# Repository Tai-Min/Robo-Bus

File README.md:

# Robo-Bus
Modular series of MCUs and hardware boards designed for robotics, providing a unified bus system for seamless and reliable communication between robotic components
test

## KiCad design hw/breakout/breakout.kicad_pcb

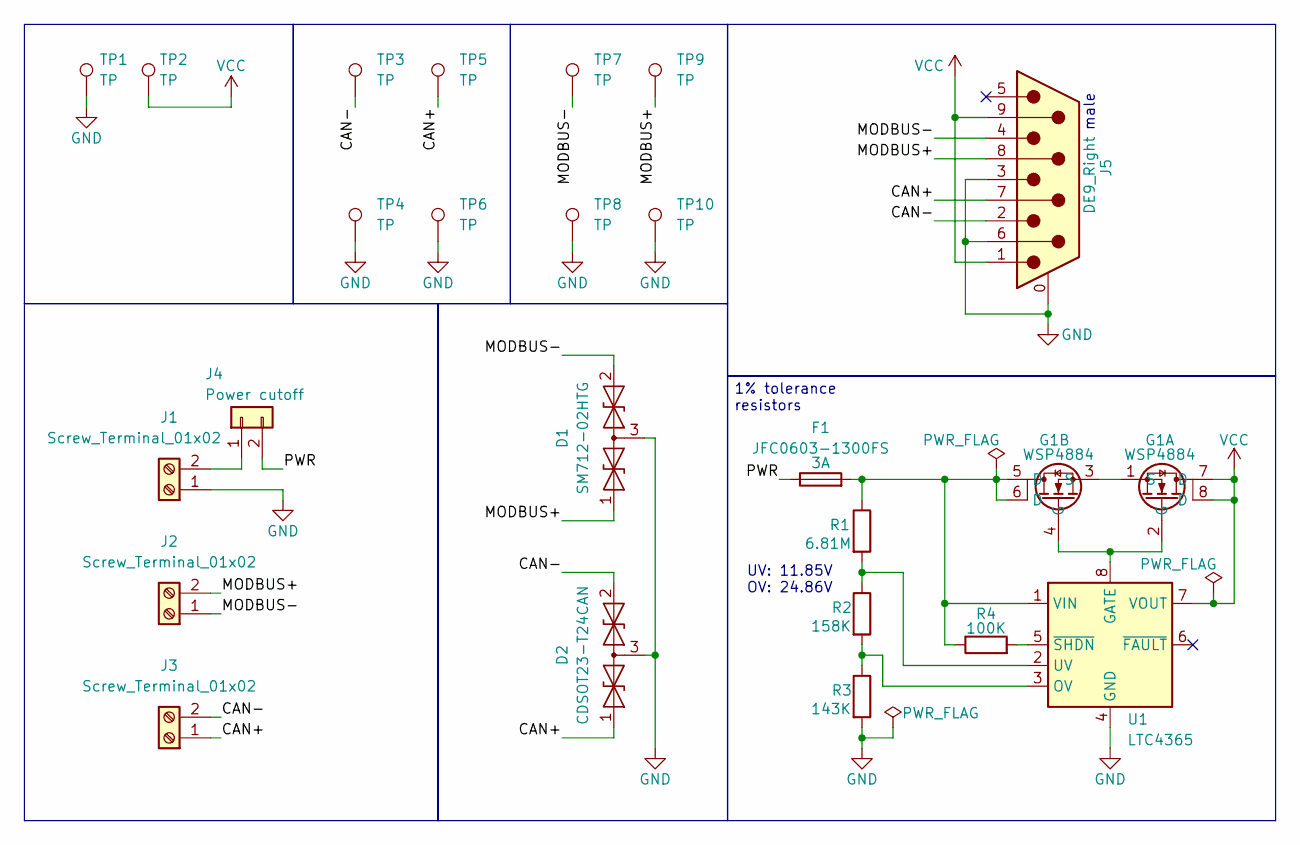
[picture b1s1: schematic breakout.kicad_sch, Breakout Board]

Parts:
D1: SM712-02HTG; SOT-23; LCSC Part # C172881
D2: CDSOT23-T24CAN; SOT-23; LCSC Part # C2959841
F1: JFC0603-1300FS; Fuse_0603_1608Metric_Pad1.05x0.95mm_HandSolder; LCSC Part # C136333
G1: WSP4884; SOIC-8_3.9x4.9mm_P1.27mm; LCSC Part # C148402
J1, J2, J3: Screw_Terminal_01x02; TerminalBlock_Phoenix_MKDS-1,5-2-5.08_1x02_P5.08mm_Horizont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; LCSC Part # C3031437
J4: Power cutoff; PinHeader_1x02_P2.54mm_Vertical; LCSC Part # C7494857
J5: DE9_Right; DSUB-9_Pins_Horizontal_P2.77x2.84mm_EdgePinOffset7.70mm_Hou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; LCSC Part # C19077344
R1: 6.81M; R_0603_1608Metric_Pad0.98x0.95mm_HandSolder; LCSC Part # C54531562
R2: 158K; R_0603_1608Metric_Pad0.98x0.95mm_HandSolder; LCSC Part # C321734
R3: 143K; R_0603_1608Metric_Pad0.98x0.95mm_HandSolder; LCSC Part # C2933146
R4: 100K; R_0603_1608Metric_Pad0.98x0.95mm_HandSolder; LCSC Part # C14675
TP1, TP2, TP3, TP4, TP5, TP6, TP7, TP8, TP9, TP10: TP; TestPoint_THTPad_D2.5mm_Drill1.2mm; LCSC Part # C5277086
U1: LTC4365; TSOT-23-8; LCSC Part # C514441

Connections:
/CAN+: D2.1 (A1), J3.1, J5.7, TP5.1 (1_1)
/CAN-: D2.2 (A2), J3.2, J5.2, TP3.1 (1_1)
/MODBUS+: D1.1 (A1), J2.2, J5.8, TP9.1 (1_1)
/MODBUS-: D1.2 (A2), J2.1, J5.4, TP7.1 (1_1)
/PWR: F1.1, J4.2
GND: D1.3 (common), D2.3 (common), J1.1, J5.0 (PAD), J5.3, J5.6, R3.2, TP1.1 (1_1), TP4.1 (1_1), TP6.1 (1_1), TP8.1 (1_1), TP10.1 (1_1), U1.4 (GND)
unnamed: G1.2 (G), G1.4 (G), U1.8 (GATE)
unnamed: G1.1 (S), G1.3 (S)
unnamed: J1.2, J4.1
unnamed: R2.2, R3.1, U1.3 (OV)
unnamed: R1.2, R2.1, U1.2 (UV)
unnamed: F1.2, G1.5 (D), G1.6 (D), R1.1, R4.1, U1.1 (VIN)
unnamed: R4.2, U1.5 (~SHDN)
VCC: G1.7 (D), G1.8 (D), J5.1, J5.9, TP2.1 (1_1), U1.7 (VOUT)

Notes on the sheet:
UV: 11.85V OV: 24.86V
male
1% tolerance resistors

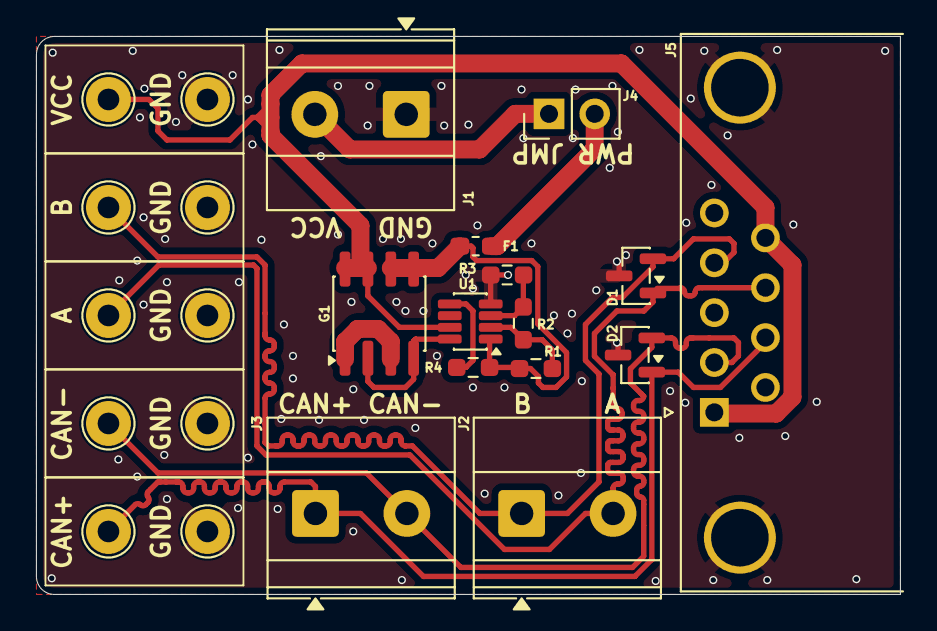
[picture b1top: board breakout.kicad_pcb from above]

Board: 2 copper layers, 48.0 x 31.0 mm, 24 parts (0 on the bottom side), 14 nets.

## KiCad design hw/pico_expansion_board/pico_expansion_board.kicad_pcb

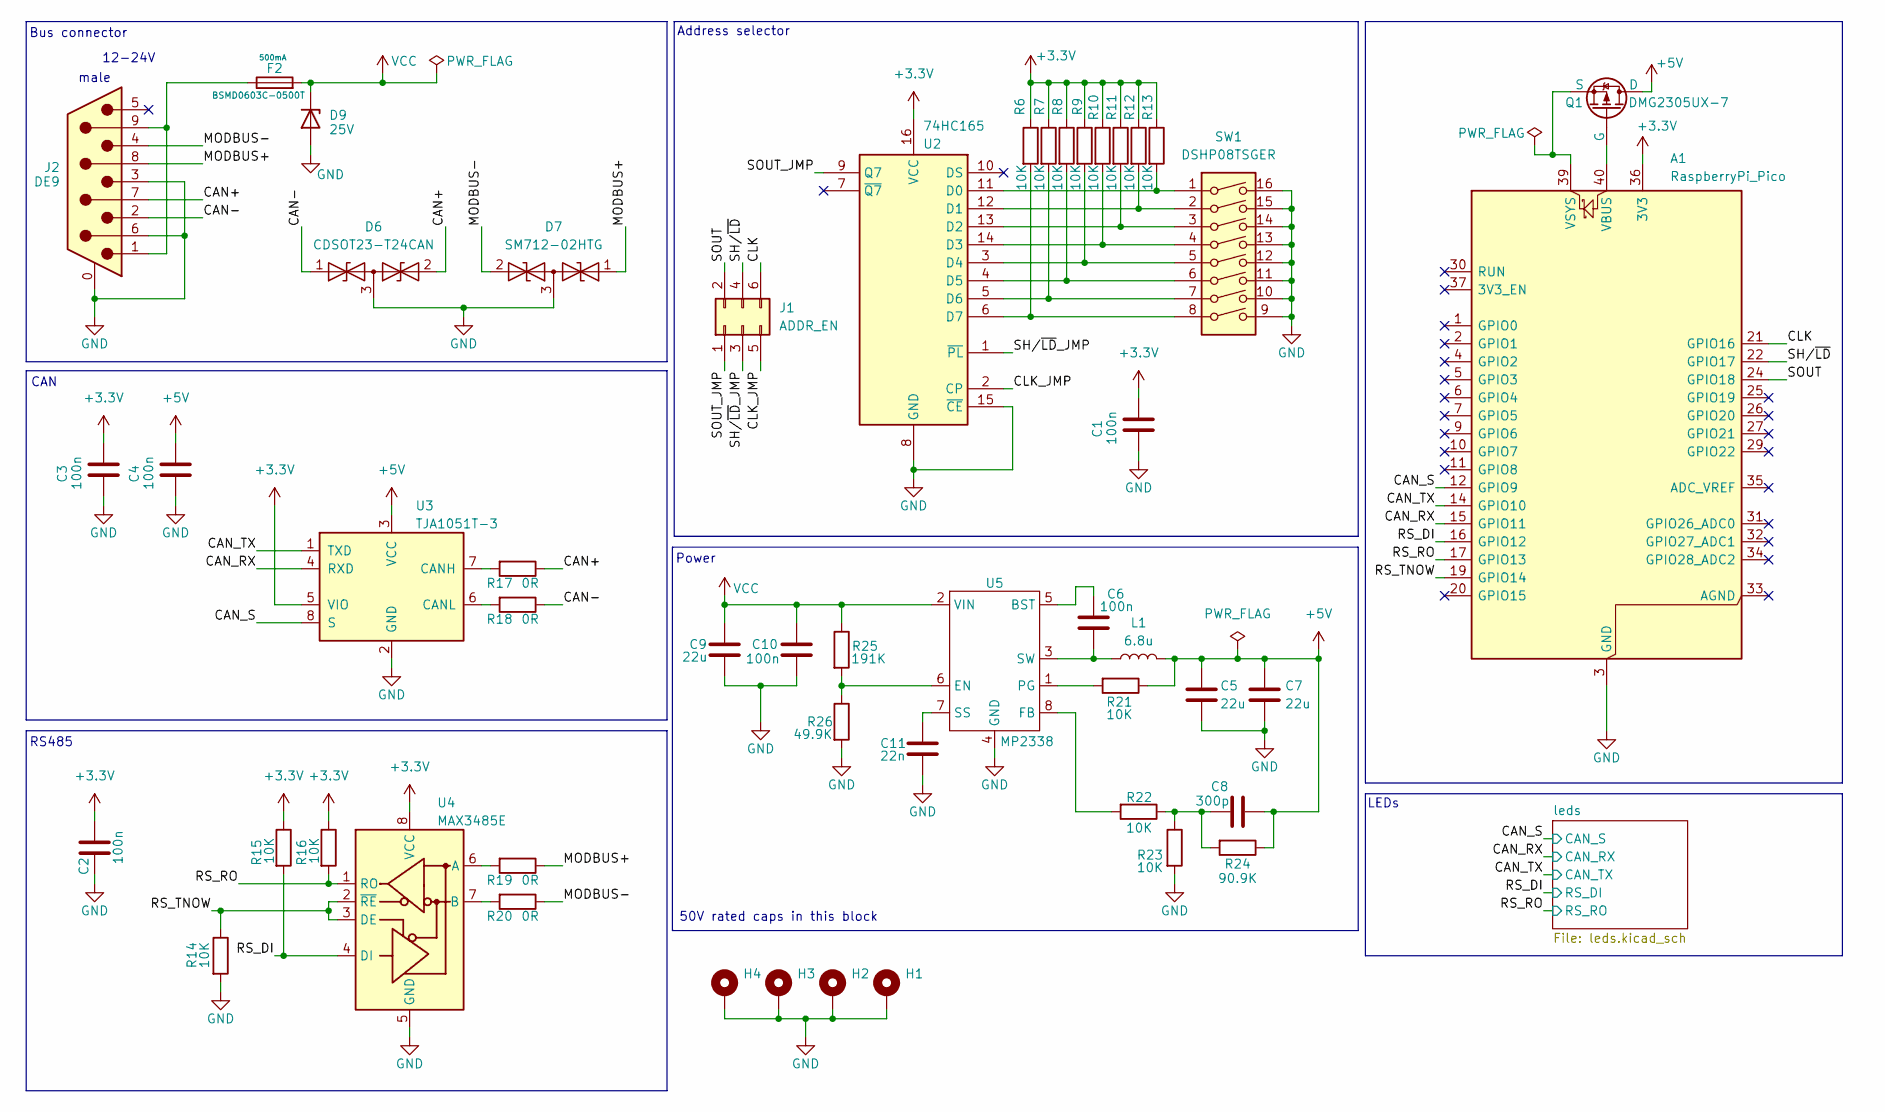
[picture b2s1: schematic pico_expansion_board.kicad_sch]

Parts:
A1: RaspberryPi_Pico; RaspberryPi_Pico_Common_Unspecified
C1, C2, C3, C4, C6, C10: 100n; C_0603_1608Metric; LCSC Part # C14663
C5, C7, C9: 22u; C_1812_4532Metric; LCSC Part # C22388553
C8: 300p; C_0603_1608Metric; LCSC Part # C913766
C11: 22n; C_0603_1608Metric; LCSC Part # C21122
D6: CDSOT23-T24CAN; SOT-23; LCSC Part # C2959841
D7: SM712-02HTG; SOT-23; LCSC Part # C172881
D9: 25V; D_SOD-123; LCSC Part # C525407
F2: BSMD0603C-0500T; Fuse_0603_1608Metric; LCSC Part # C41380225
H1, H2, H3, H4: MountingHole_Pad; MountingHole_3.2mm_M3_Pad_Via
J1: ADDR_EN; PinHeader_2x03_P2.54mm_Vertical; LCSC Part # C7494874
J2: DE9; DSUB-9_Pins_Horizontal_P2.77x2.84mm_EdgePinOffset7.70mm_Hou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; LCSC Part # C19077344
L1: 6.8u; L_APV_ANR4010; LCSC Part # C497571
Q1: DMG2305UX-7; SC-59; LCSC Part # C150470
R6, R7, R8, R9, R10, R11, R12, R13, R14, R15, R16, R21, R22, R23: 10K; R_0603_1608Metric; LCSC Part # C98220
R17, R18, R19, R20: 0R; R_0603_1608Metric; LCSC Part # C95177
R24: 90.9K; R_0603_1608Metric; LCSC Part # C2930136
R25: 191K; R_0603_1608Metric; LCSC Part # C22932
R26: 49.9K; R_0603_1608Metric; LCSC Part # C114624
SW1: DSHP08TSGER; SW_DIP_SPSTx08_Slide_KingTek_DSHP08TS_W7.62mm_P1.27mm; LCSC Part # C3293147
U2: 74HC165; TSSOP-16_4.4x5mm_P0.65mm; LCSC Part # C43420
U3: TJA1051T-3; SOIC-8_3.9x4.9mm_P1.27mm; LCSC Part # C51954344
U4: MAX3485E; SOIC-8_3.9x4.9mm_P1.27mm; LCSC Part # C41369523
U5: MP2338; SOT-583-8

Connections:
+3.3V: A1.36 (3V3), C1.2, C2.2, C3.2, R6.1, R7.1, R8.1, R9.1, R10.1, R11.1, R12.1, R13.1, R15.1, R16.1, U2.16 (VCC), U3.5 (VIO), U4.8 (VCC)
+5V: C4.2, C5.1, C7.1, C8.2, L1.2, Q1.1 (D), R21.1, R24.1, U3.3 (VCC); also elsewhere on the board
/CAN+: D6.2 (A2), J2.7, R17.1
/CAN-: D6.1 (A1), J2.2, R18.1
/CAN_RX: A1.15 (GPIO11), U3.4 (RXD); also elsewhere on the board
/CAN_S: A1.12 (GPIO9), U3.8 (S); also elsewhere on the board
/CAN_TX: A1.14 (GPIO10), U3.1 (TXD); also elsewhere on the board
/CLK: A1.21 (GPIO16), J1.6
/CLK_JMP: J1.5, U2.2 (CP)
/MODBUS+: D7.1 (A1), J2.8, R19.1
/MODBUS-: D7.2 (A2), J2.4, R20.1
/RS_DI: A1.16 (GPIO12), R15.2, U4.4 (DI); also elsewhere on the board
/RS_RO: A1.17 (GPIO13), R16.2, U4.1 (RO); also elsewhere on the board
/RS_TNOW: A1.19 (GPIO14), R14.1, U4.2 (~RE), U4.3 (DE)
/SH/~LD: A1.22 (GPIO17), J1.4
/SH/~LD_JMP: J1.3, U2.1 (~PL)
/SOUT: A1.24 (GPIO18), J1.2
/SOUT_JMP: J1.1, U2.9 (Q7)
GND: A1.3 (GND), A1.8 (GND), A1.13 (GND), A1.18 (GND), A1.23 (GND), A1.28 (GND), A1.38 (GND), C1.1, C2.1, C3.1, C4.1, C5.2, C7.2, C9.2, C10.1, C11.2, D6.3 (common), D7.3 (common), D9.2 (A), H1.1, H2.1, H3.1, H4.1, J2.0 (PAD), J2.3, J2.6, R14.2, R23.2, R26.2, SW1.9, SW1.10, SW1.11, SW1.12, SW1.13, SW1.14, SW1.15, SW1.16, U2.8 (GND), U2.15 (~CE), U3.2 (GND), U4.5 (GND), U5.4 (GND); also elsewhere on the board
unnamed: A1.40 (VBUS), Q1.2 (G)
unnamed: A1.39 (VSYS), Q1.3 (S)
unnamed: C8.1, R22.1, R23.1, R24.2
unnamed: F2.1, J2.1, J2.9
unnamed: R13.2, SW1.1, U2.11 (D0)
unnamed: R12.2, SW1.2, U2.12 (D1)
unnamed: R11.2, SW1.3, U2.13 (D2)
unnamed: R10.2, SW1.4, U2.14 (D3)
unnamed: R9.2, SW1.5, U2.3 (D4)
unnamed: R8.2, SW1.6, U2.4 (D5)
unnamed: R7.2, SW1.7, U2.5 (D6)
unnamed: R6.2, SW1.8, U2.6 (D7)
unnamed: R17.2, U3.7 (CANH)
unnamed: R18.2, U3.6 (CANL)
unnamed: R19.2, U4.6 (A)
unnamed: R20.2, U4.7 (B)
unnamed: C6.2, U5.5 (BST)
unnamed: R25.2, R26.1, U5.6 (EN)
unnamed: R22.2, U5.8 (FB)
unnamed: R21.2, U5.1 (PG)
unnamed: C11.1, U5.7 (SS)
unnamed: C6.1, L1.1, U5.3 (SW)
VCC: C9.1, C10.2, D9.1 (K), F2.2, R25.1, U5.2 (VIN)

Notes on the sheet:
CAN
LEDs
12-24V
50V rated caps in this block
Bus connector
Address selector
male
RS485
Power

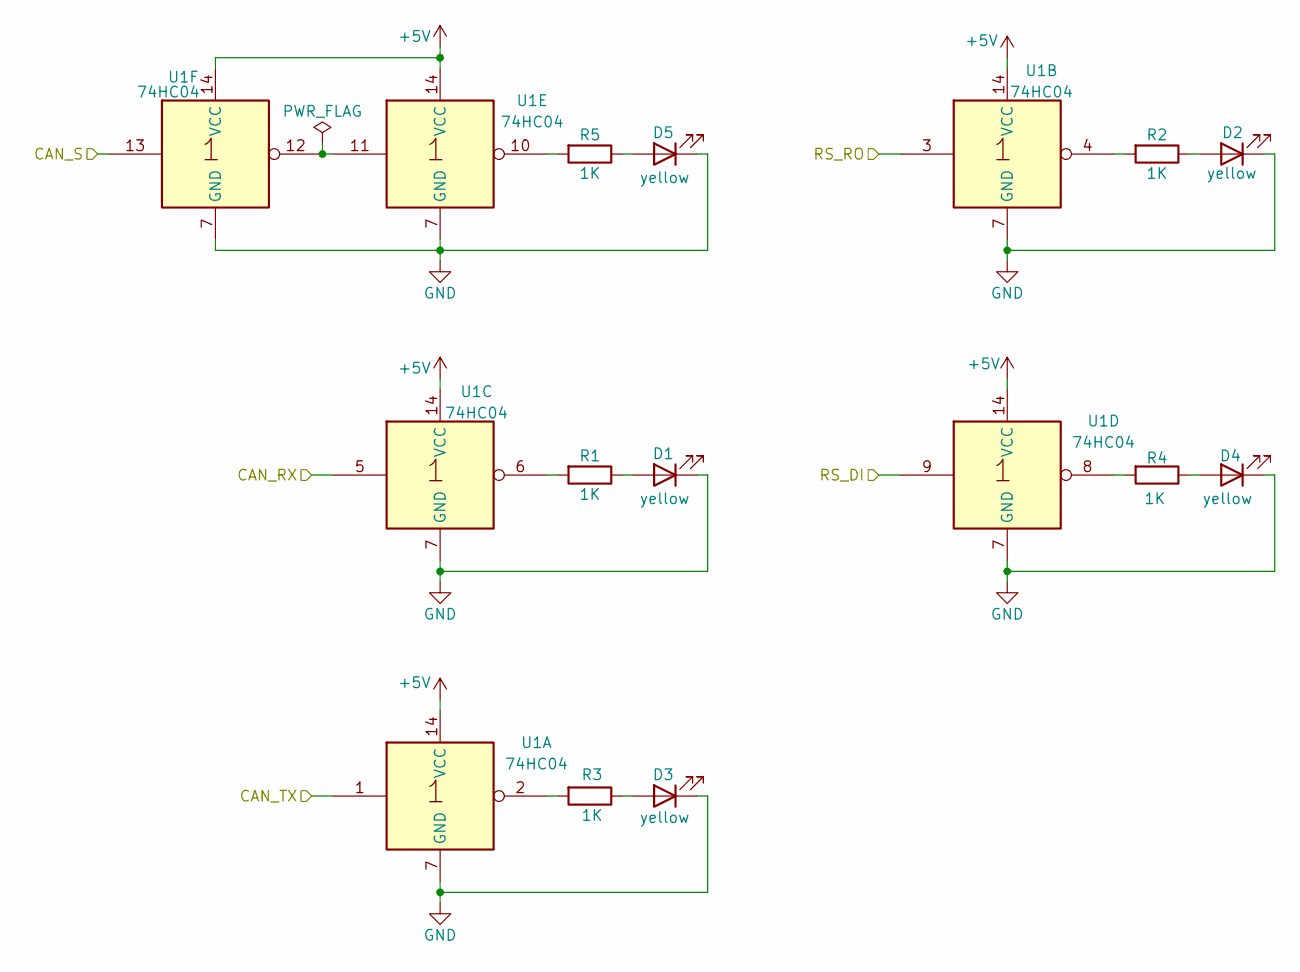
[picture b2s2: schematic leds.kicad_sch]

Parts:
D1, D2, D3, D4, D5: yellow; LED_0603_1608Metric; LCSC Part # C72038
R1, R2, R3, R4, R5: 1K; R_0603_1608Metric; LCSC Part # C22548
U1: 74HC04; TSSOP-14_4.4x5mm_P0.65mm; LCSC Part # C19723773

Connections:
+5V: U1.14 (VCC); also elsewhere on the board
/CAN_RX: U1.5; also elsewhere on the board
/CAN_S: U1.13; also elsewhere on the board
/CAN_TX: U1.1; also elsewhere on the board
/RS_DI: U1.9; also elsewhere on the board
/RS_RO: U1.3; also elsewhere on the board
GND: D1.1 (K), D2.1 (K), D3.1 (K), D4.1 (K), D5.1 (K), U1.7 (GND); also elsewhere on the board
unnamed: D1.2 (A), R1.1
unnamed: D2.2 (A), R2.1
unnamed: D3.2 (A), R3.1
unnamed: D4.2 (A), R4.1
unnamed: D5.2 (A), R5.1
unnamed: R1.2, U1.6
unnamed: R2.2, U1.4
unnamed: R3.2, U1.2
unnamed: R4.2, U1.8
unnamed: R5.2, U1.10
unnamed: U1.11, U1.12

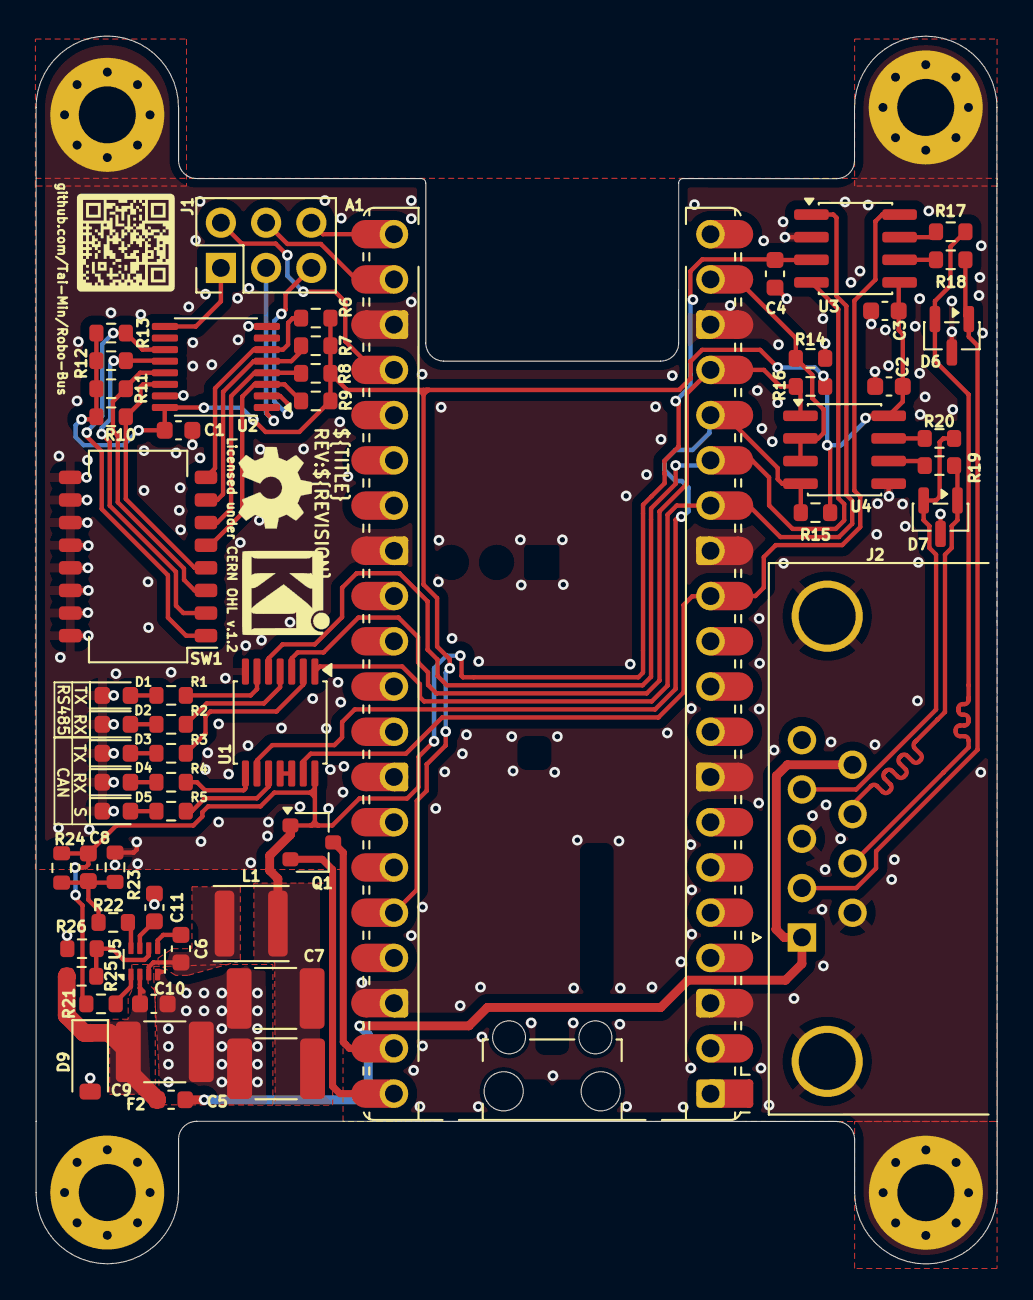
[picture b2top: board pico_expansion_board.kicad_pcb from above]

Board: 2 copper layers, 54.0 x 69.0 mm, 62 parts (0 on the bottom side), 53 nets.

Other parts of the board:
osh: OSHW-Logo2_7.3x6mm_SilkScreen

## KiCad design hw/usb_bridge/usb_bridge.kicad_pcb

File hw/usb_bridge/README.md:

USB <--> CAN part of this pcb is based on [candleLight FD](https://github.com/linux-automation/candleLightFD/tree/main).

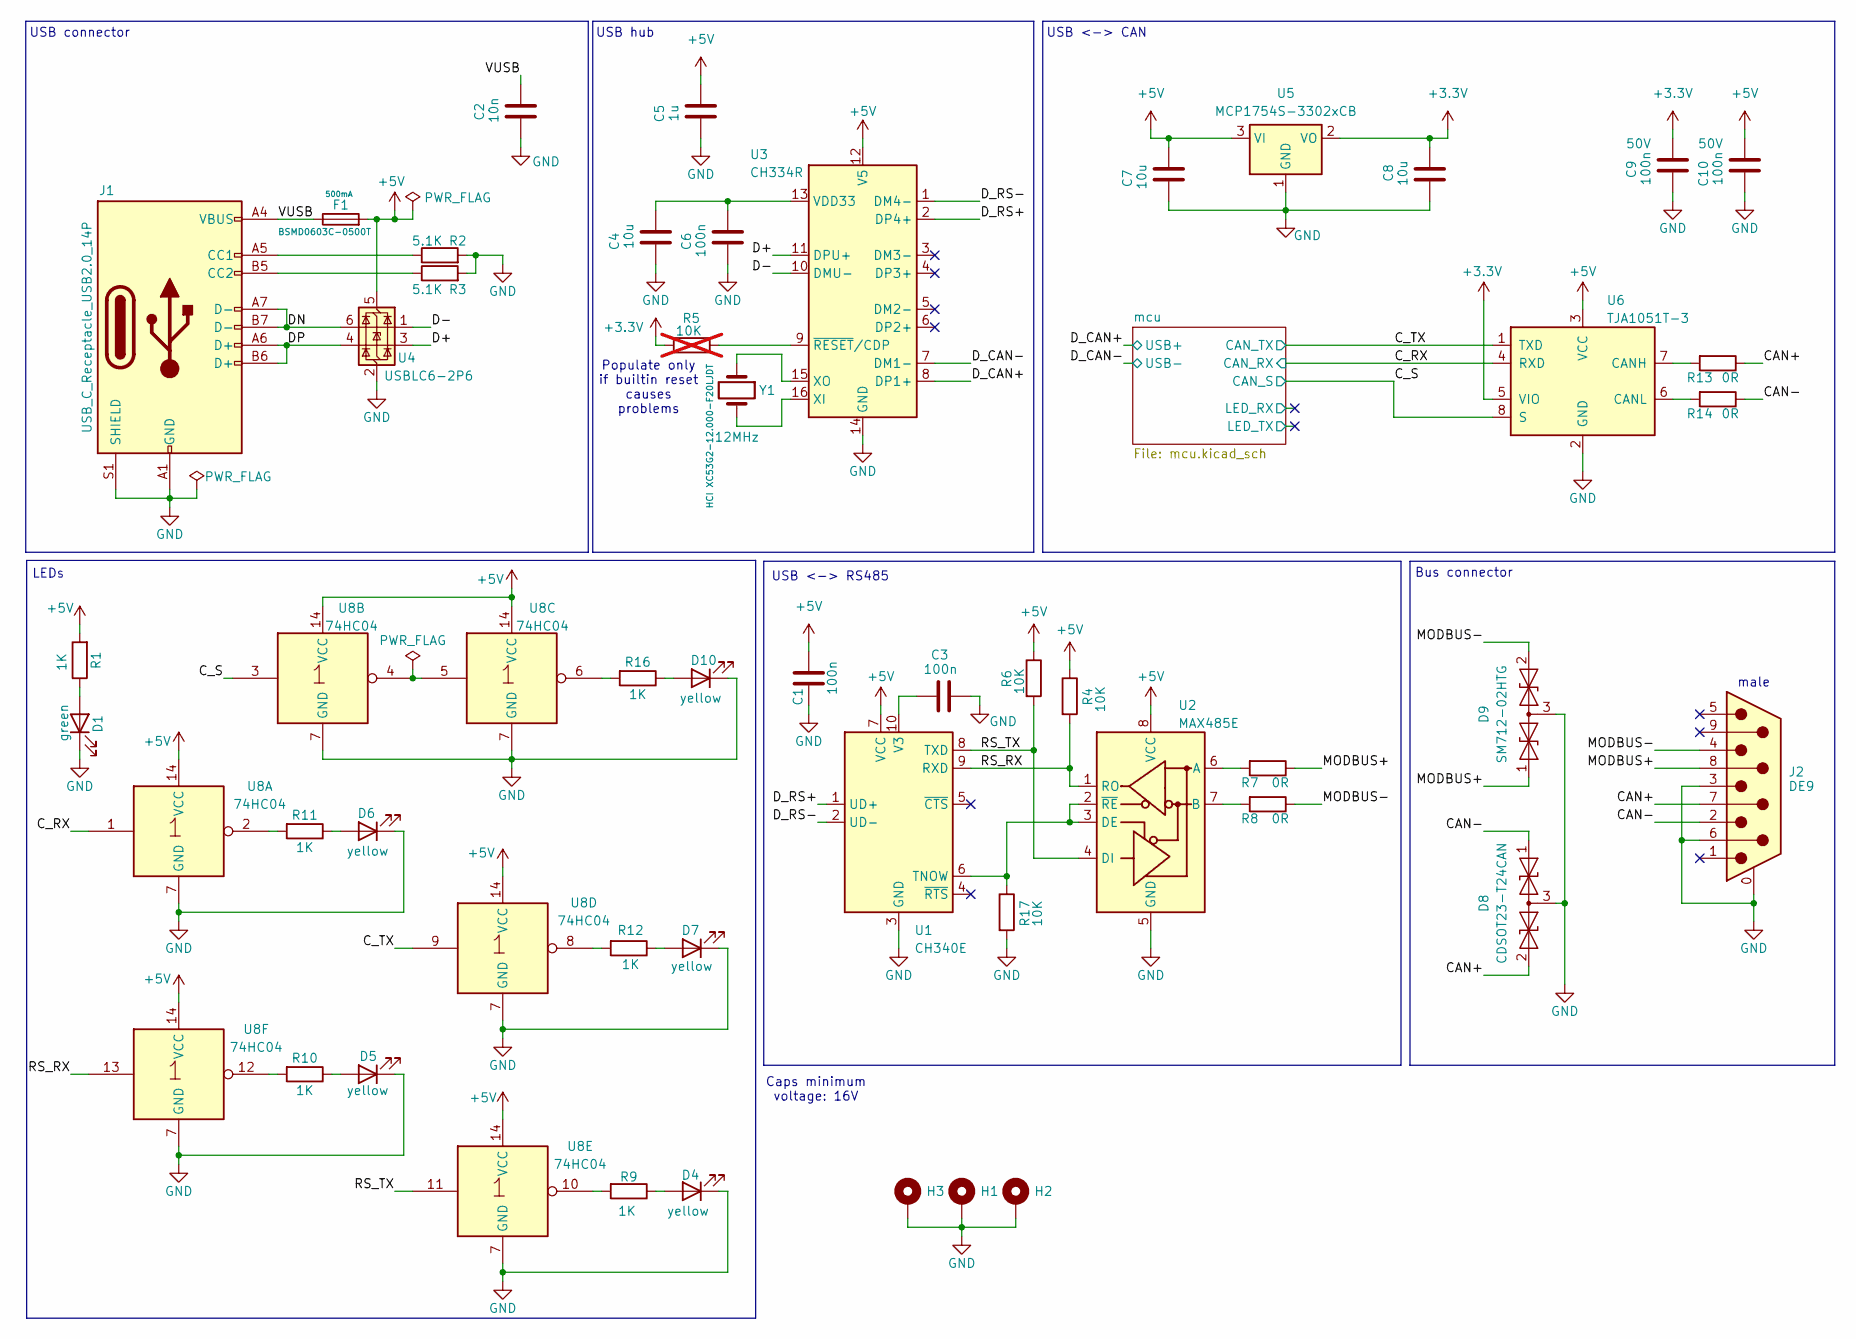
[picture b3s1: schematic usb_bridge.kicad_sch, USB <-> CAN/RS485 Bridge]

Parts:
C1, C3, C6, C9, C10: 100n; C_0603_1608Metric; LCSC Part # C66501
C2: 10n; C_0603_1608Metric; LCSC Part # C100042
C4, C7, C8: 10u; C_0603_1608Metric; LCSC Part # C92487
C5: 1u; C_0603_1608Metric; LCSC Part # C1592
D1: green; LED_0603_1608Metric; LCSC Part # C22371297
D4, D5, D6, D7, D10: yellow; LED_0603_1608Metric; LCSC Part # C72038
D8: CDSOT23-T24CAN; SOT-23; LCSC Part # C2959841
D9: SM712-02HTG; SOT-23; LCSC Part # C172881
F1: BSMD0603C-0500T; Fuse_0603_1608Metric; LCSC Part # C41380225
H1, H2, H3: MountingHole_Pad; MountingHole_3.2mm_M3_Pad_Via
J1: USB_C_Receptacle_USB2.0_14P; USB_C_Receptacle_GCT_USB4085; LCSC Part # C7095263
J2: DE9; DSUB-9_Pins_Horizontal_P2.77x2.84mm_EdgePinOffset7.70mm_Hou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; LCSC Part # C19077344
R1, R9, R10, R11, R12, R16: 1K; R_0603_1608Metric; LCSC Part # C22548
R2, R3: 5.1K; R_0603_1608Metric; LCSC Part # C2907044
R4, R6, R17: 10K; R_0603_1608Metric; LCSC Part # C98220
R5: 10K; R_0603_1608Metric; LCSC Part # C98220; not fitted
R7, R8, R13, R14: 0R; R_0603_1608Metric; LCSC Part # C95177
U1: CH340E; MSOP-10_3x3mm_P0.5mm; LCSC Part # C99652
U2: MAX485E; SOIC-8_3.9x4.9mm_P1.27mm; LCSC Part # C481667
U3: CH334R; QSOP-16_3.9x4.9mm_P0.635mm; LCSC Part # C4154405
U4: USBLC6-2P6; SOT-666; LCSC Part # C15999
U5: MCP1754S-3302xCB; SOT-23; LCSC Part # C625392
U6: TJA1051T-3; SOIC-8_3.9x4.9mm_P1.27mm; LCSC Part # C51954344
U8: 74HC04; TSSOP-14_4.4x5mm_P0.65mm; LCSC Part # C19723773
Y1: HCI XC53G2-12.000-F20LJDT; Crystal_SMD_5032-2Pin_5.0x3.2mm; LCSC Part # C2842275

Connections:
+3.3V: C8.2, C9.2, R5.2, U5.2 (VO), U6.5 (VIO); also elsewhere on the board
+5V: C1.2, C5.2, C7.2, C10.2, F1.2, R1.2, R4.1, R6.1, U1.7 (VCC), U2.8 (VCC), U3.12 (V5), U4.5 (VBUS), U5.3 (VI), U6.3 (VCC), U8.14 (VCC)
/CAN+: D8.2 (A2), J2.7, R13.1
/CAN-: D8.1 (A1), J2.2, R14.1
/C_RX: U6.4 (RXD), U8.1; also elsewhere on the board
/C_S: U6.8 (S), U8.3; also elsewhere on the board
/C_TX: U6.1 (TXD), U8.9; also elsewhere on the board
/D+: U3.11 (DPU+), U4.3 (I/O2)
/D-: U3.10 (DMU-), U4.1 (I/O1)
/DN: J1.A7 (D-), J1.B7 (D-), U4.6 (I/O1)
/DP: J1.A6 (D+), J1.B6 (D+), U4.4 (I/O2)
/D_CAN+: U3.8 (DP1+); also elsewhere on the board
/D_CAN-: U3.7 (DM1-); also elsewhere on the board
/D_RS+: U1.1 (UD+), U3.2 (DP4+)
/D_RS-: U1.2 (UD-), U3.1 (DM4-)
/MODBUS+: D9.1 (A1), J2.8, R7.1
/MODBUS-: D9.2 (A2), J2.4, R8.1
/RS_RX: R4.2, U1.9 (RXD), U2.1 (RO), U8.13
/RS_TX: R6.2, U1.8 (TXD), U2.4 (DI), U8.11
/VUSB: C2.2, F1.1, J1.A4 (VBUS), J1.A9 (VBUS), J1.B4 (VBUS), J1.B9 (VBUS)
GND: C1.1, C2.1, C3.2, C4.1, C5.1, C6.1, C7.1, C8.1, C9.1, C10.1, D1.1 (K), D4.1 (K), D5.1 (K), D6.1 (K), D7.1 (K), D8.3 (common), D9.3 (common), D10.1 (K), H1.1, H2.1, H3.1, J1.A1 (GND), J1.A12 (GND), J1.B1 (GND), J1.B12 (GND), J1.S1 (SHIELD), J2.0 (PAD), J2.3, J2.6, R2.2, R3.2, R17.2, U1.3 (GND), U2.5 (GND), U3.14 (GND), U4.2 (GND), U5.1 (GND), U6.2 (GND), U8.7 (GND); also elsewhere on the board
unnamed: D1.2 (A), R1.1
unnamed: D4.2 (A), R9.1
unnamed: D5.2 (A), R10.1
unnamed: D6.2 (A), R11.1
unnamed: D7.2 (A), R12.1
unnamed: D10.2 (A), R16.1
unnamed: J1.A5 (CC1), R2.1
unnamed: J1.B5 (CC2), R3.1
unnamed: R9.2, U8.10
unnamed: R10.2, U8.12
unnamed: R11.2, U8.2
unnamed: R12.2, U8.8
unnamed: R16.2, U8.6
unnamed: R17.1, U1.6 (TNOW), U2.2 (~RE), U2.3 (DE)
unnamed: C3.1, U1.10 (V3)
unnamed: R7.2, U2.6 (A)
unnamed: R8.2, U2.7 (B)
unnamed: C4.2, C6.2, U3.13 (VDD33)
unnamed: U3.16 (XI), Y1.2
unnamed: U3.15 (XO), Y1.1
unnamed: R5.1, U3.9 (~RESET/CDP)
unnamed: R13.2, U6.7 (CANH)
unnamed: R14.2, U6.6 (CANL)
unnamed: U8.4, U8.5

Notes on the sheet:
Populate only if builtin reset causes problems
USB <-> RS485
Bus connector
male
USB <-> CAN
USB hub
Caps minimum voltage: 16V
LEDs
USB connector

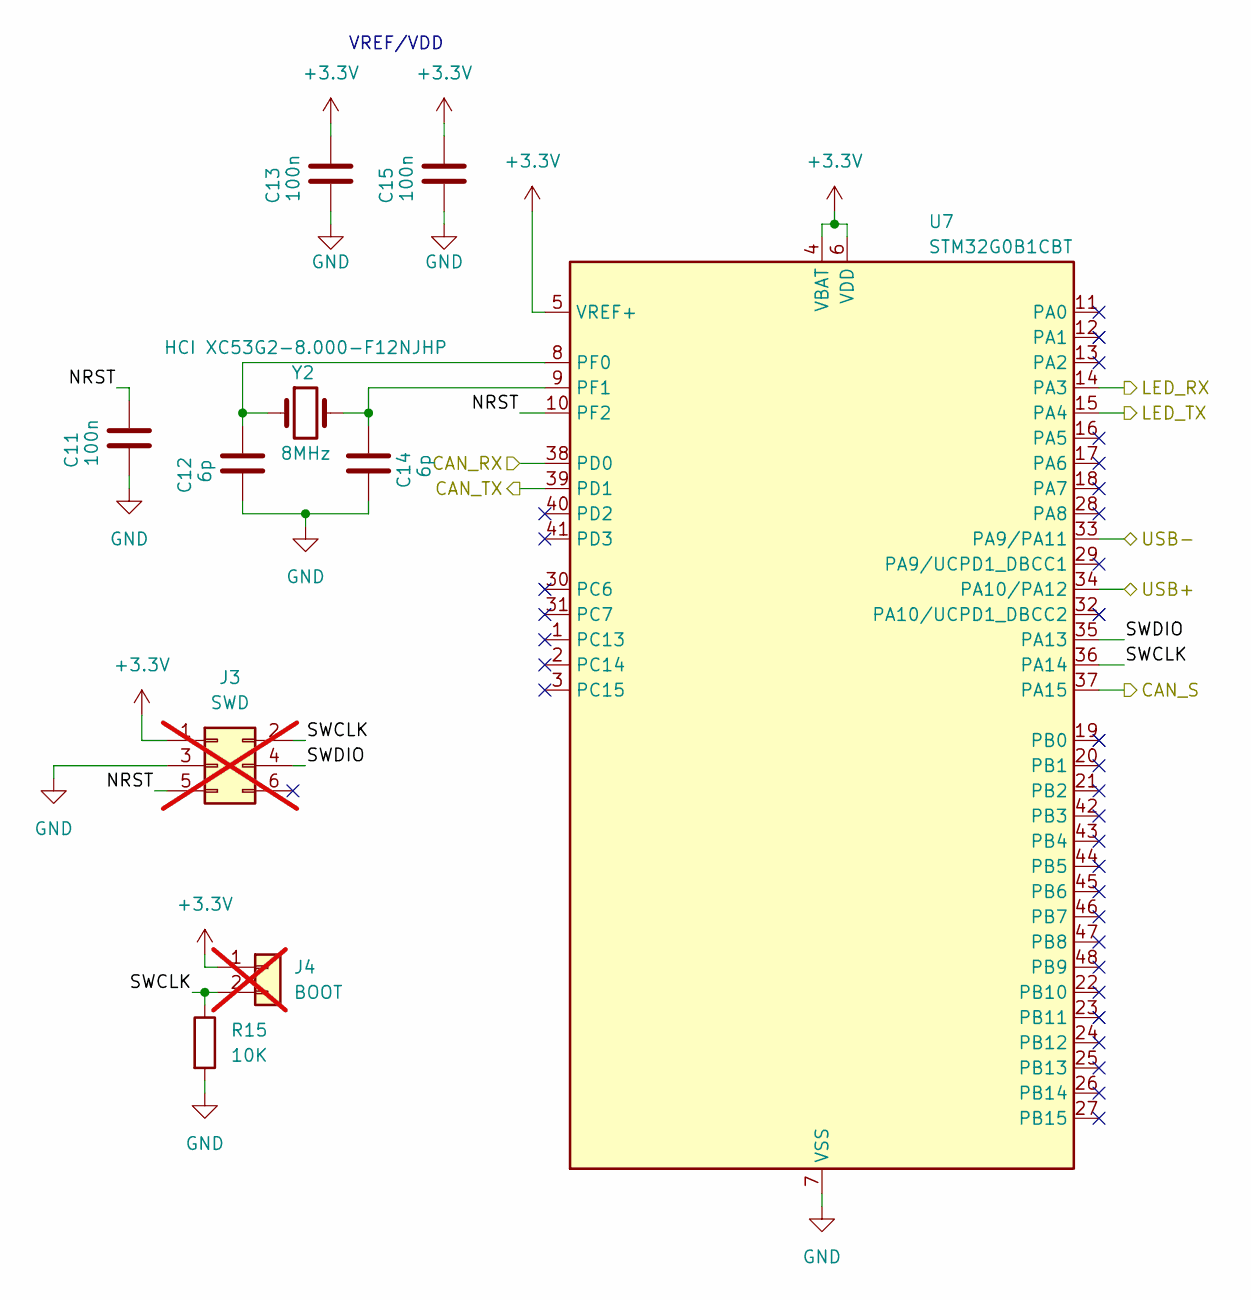
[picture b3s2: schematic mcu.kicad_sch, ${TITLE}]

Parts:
C11, C13, C15: 100n; C_0603_1608Metric; LCSC Part # C66501
C12, C14: 6p; C_0603_1608Metric; LCSC Part # C170142
J3: SWD; PinHeader_2x03_P2.54mm_Vertical; LCSC Part # C7494874; not fitted
J4: BOOT; PinHeader_1x02_P2.54mm_Vertical; LCSC Part # C7494857; not fitted
R15: 10K; R_0603_1608Metric; LCSC Part # C98220
U7: STM32G0B1CBT; LQFP-48_7x7mm_P0.5mm; LCSC Part # C2847904
Y2: HCI XC53G2-8.000-F12NJHP; Crystal_SMD_5032-2Pin_5.0x3.2mm; LCSC Part # C2842269

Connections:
+3.3V: C13.2, C15.2, J3.1, J4.1, U7.4 (VBAT), U7.5 (VREF+), U7.6 (VDD); also elsewhere on the board
/C_RX: U7.38 (PD0); also elsewhere on the board
/C_S: U7.37 (PA15); also elsewhere on the board
/C_TX: U7.39 (PD1); also elsewhere on the board
/D_CAN+: U7.34 (PA10/PA12); also elsewhere on the board
/D_CAN-: U7.33 (PA9/PA11); also elsewhere on the board
/mcu/LED_RX: U7.14 (PA3)
/mcu/LED_TX: U7.15 (PA4)
/mcu/NRST: C11.2, J3.5, U7.10 (PF2)
/mcu/SWCLK: J3.2, J4.2, R15.1, U7.36 (PA14)
/mcu/SWDIO: J3.4, U7.35 (PA13)
GND: C11.1, C12.1, C13.1, C14.1, C15.1, J3.3, R15.2, U7.7 (VSS); also elsewhere on the board
unnamed: C12.2, U7.8 (PF0), Y2.1
unnamed: C14.2, U7.9 (PF1), Y2.2

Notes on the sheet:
VREF/VDD

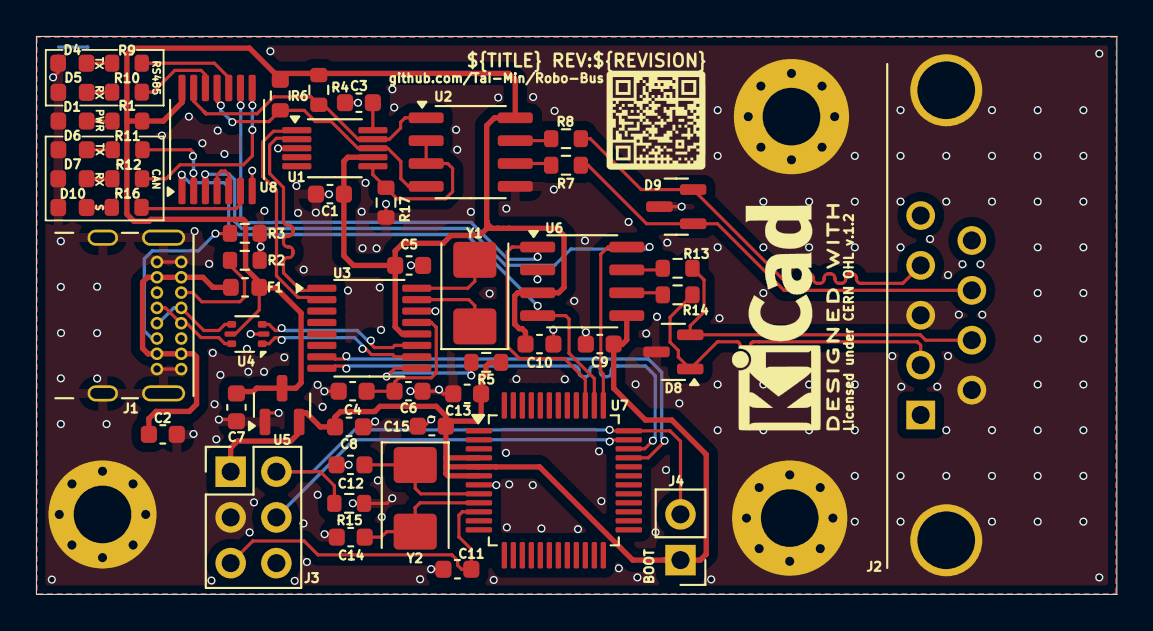
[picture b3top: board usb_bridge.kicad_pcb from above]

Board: 2 copper layers, 60.0 x 31.0 mm, 58 parts (0 on the bottom side), 50 nets.

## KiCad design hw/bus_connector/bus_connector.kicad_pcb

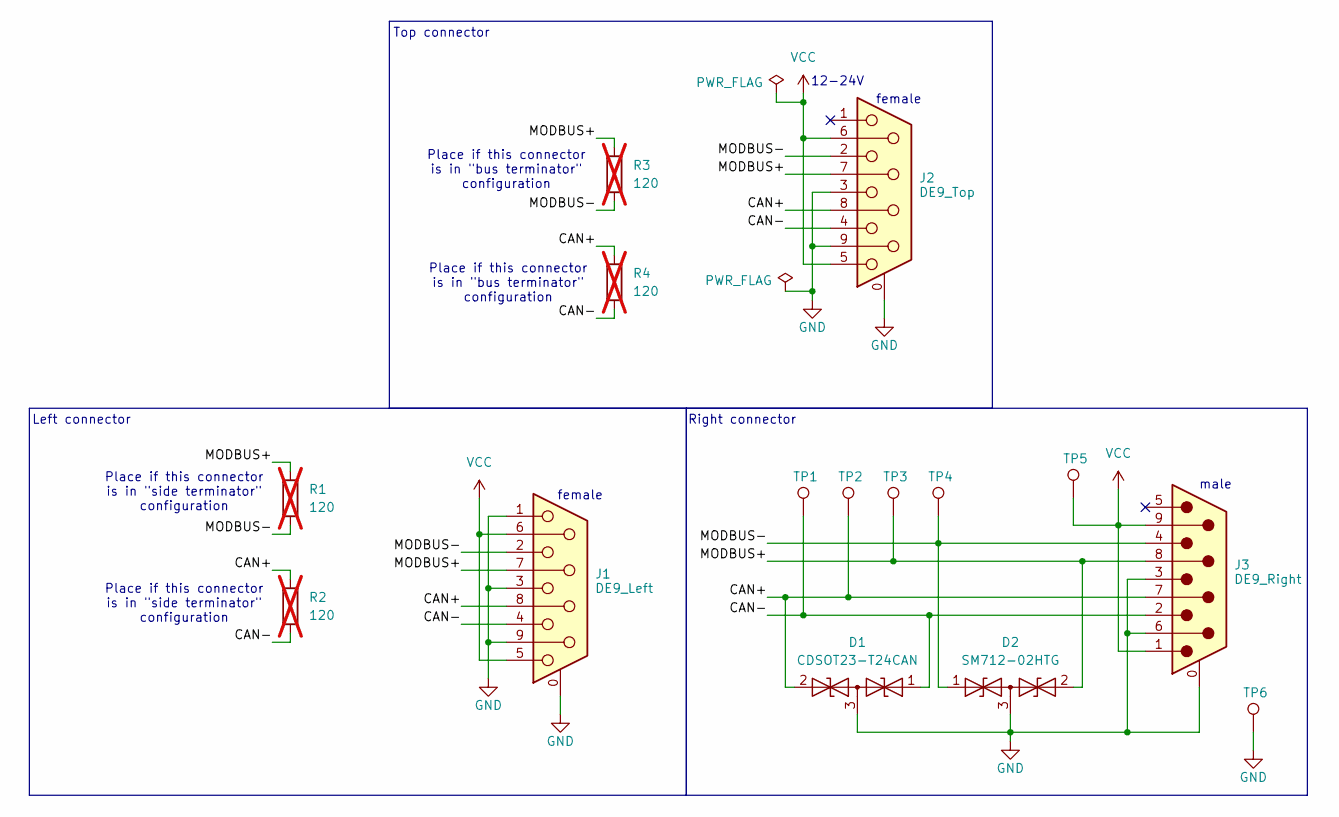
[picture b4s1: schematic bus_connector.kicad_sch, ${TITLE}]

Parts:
D1: CDSOT23-T24CAN; SOT-23; LCSC Part # C2959841
D2: SM712-02HTG; SOT-23; LCSC Part # C172881
J1: DE9_Left; DSUB-9_Pins_Horizontal_P2.77x2.84mm_EdgePinOffset7.70mm_Hou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; LCSC Part # C19077337
J2: DE9_Top; DSUB-9_Pins_Horizontal_P2.77x2.84mm_EdgePinOffset7.70mm_Hou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; LCSC Part # C19077337
J3: DE9_Right; DSUB-9_Pins_Horizontal_P2.77x2.84mm_EdgePinOffset7.70mm_Hou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; LCSC Part # C19077344
R1, R2, R3, R4: 120; R_1206_3216Metric; LCSC Part # C114928; not fitted
TP1, TP2, TP3, TP4, TP5, TP6: TestPoint; TestPoint_Pad_D1.5mm

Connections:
/CAN+: D1.2 (A2), J1.8, J2.8, J3.7, R2.2, R4.2, TP2.1
/CAN-: D1.1 (A1), J1.4, J2.4, J3.2, R2.1, R4.1, TP1.1
/MODBUS+: D2.2 (A2), J1.7, J2.7, J3.8, R1.2, R3.2, TP3.1
/MODBUS-: D2.1 (A1), J1.2, J2.2, J3.4, R1.1, R3.1, TP4.1
GND: D1.3 (common), D2.3 (common), J1.0 (PAD), J1.1, J1.3, J1.9, J2.0 (PAD), J2.3, J2.9, J3.0 (PAD), J3.3, J3.6, TP6.1
VCC: J1.5, J1.6, J2.5, J2.6, J3.1, J3.9, TP5.1

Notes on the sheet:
Place if this connector is in "side terminator" configuration
Top connector
female
12-24V
Place if this connector is in "bus terminator" configuration
Right connector
Left connector
male

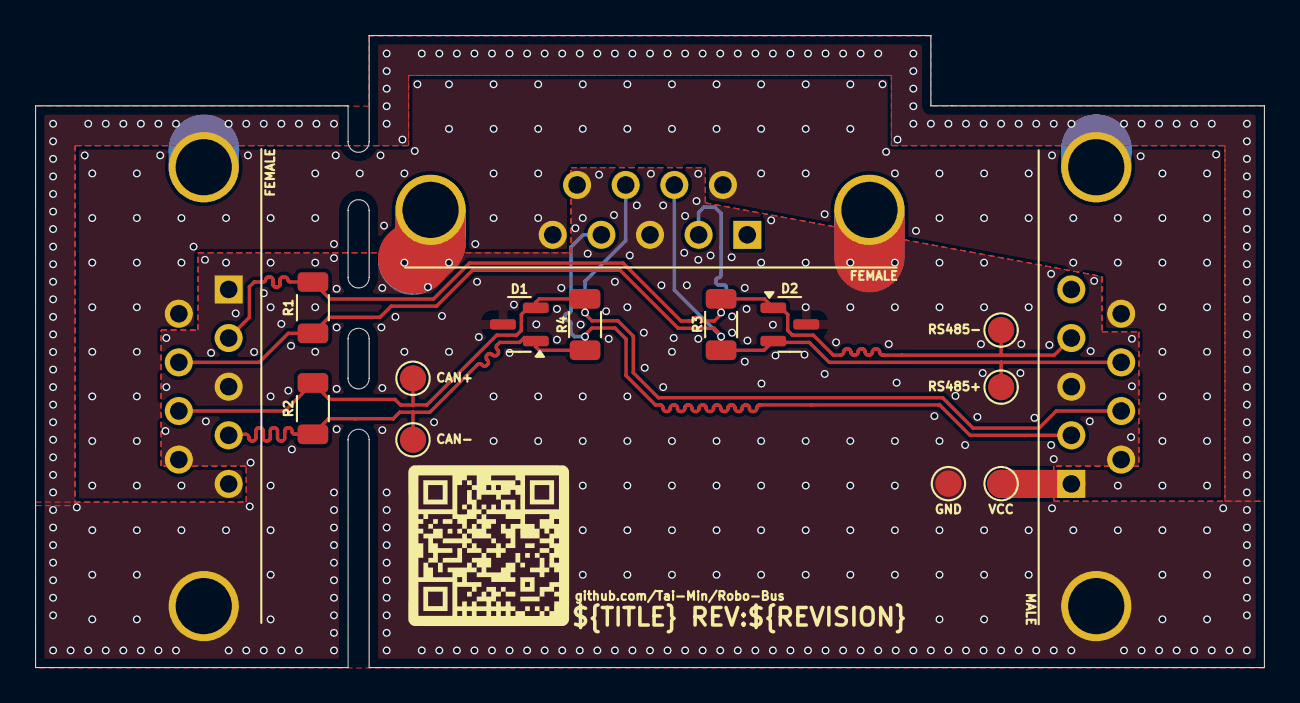
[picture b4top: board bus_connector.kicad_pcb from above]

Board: 2 copper layers, 70.0 x 36.0 mm, 15 parts (0 on the bottom side), 6 nets.

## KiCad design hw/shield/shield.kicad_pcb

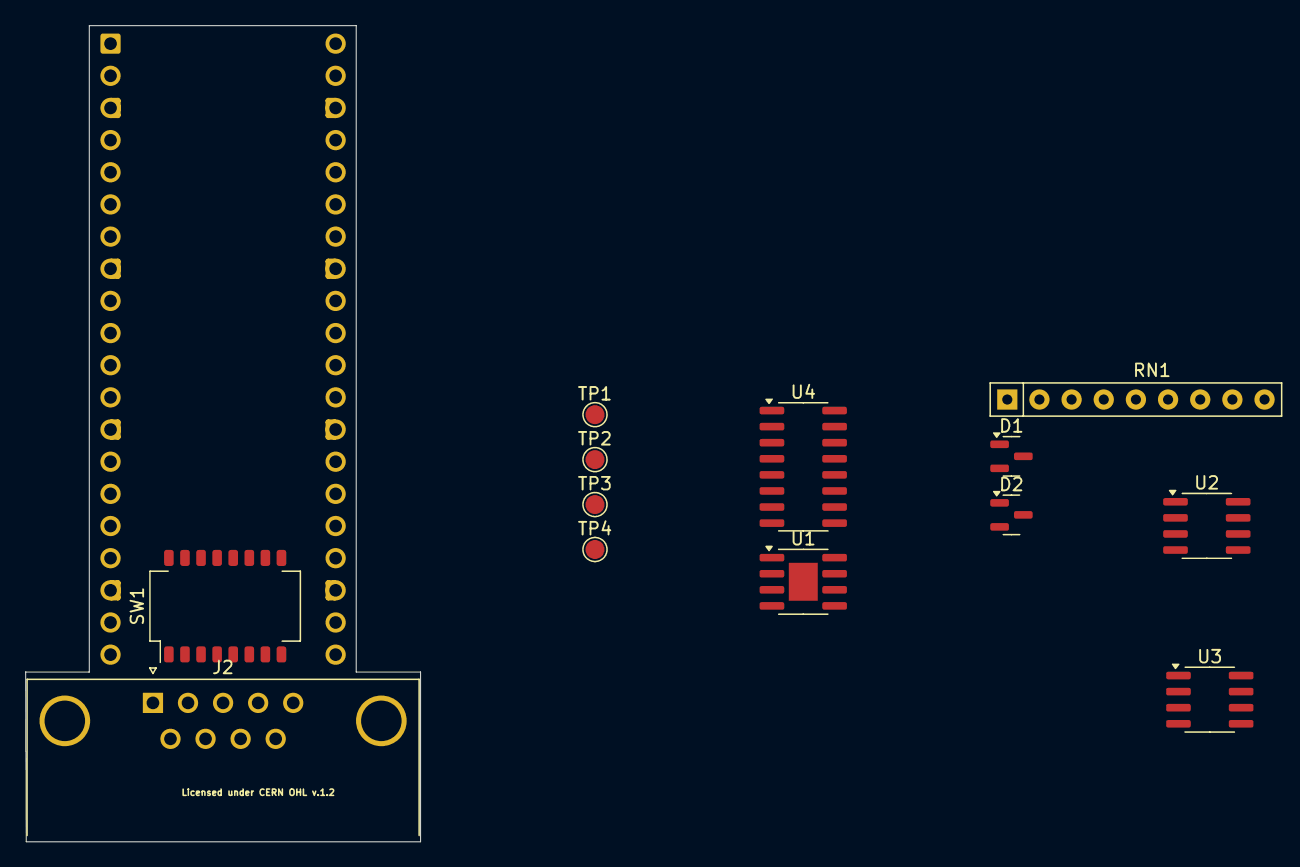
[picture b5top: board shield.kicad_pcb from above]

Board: 2 copper layers, 31.2 x 64.5 mm, 14 parts (0 on the bottom side), 16 nets, no tracks yet.

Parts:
A2: RaspberryPi_Pico; RaspberryPi_Pico_Common_Unspecified
D1: CDSOT23-T24CAN; SOT-23
D2: SM712-02HTG; SOT-23
J2: DE9; DSUB-9_Pins_Horizontal_P2.77x2.84mm_EdgePinOffset7.70mm_Hou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
RN1: 10K; R_Array_SIP9
SW1: SW_DIP_x08; SW_DIP_SPSTx08_Slide_KingTek_DSHP08TS_W7.62mm_P1.27mm
TP1, TP2, TP3, TP4: TestPoint; TestPoint_Pad_D1.5mm
U1: TCAN330G; SOIC-8-1EP_3.9x4.9mm_P1.27mm_EP2.29x3mm
U2: MAX485E; SOIC-8_3.9x4.9mm_P1.27mm
U3: TPS5405DR; SOIC-8_3.9x4.9mm_P1.27mm
U4: 74HC165; SOIC-16_3.9x9.9mm_P1.27mm

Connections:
+3.3V: A2.36 (3V3), RN1.1 (common), U1.3 (VCC), U2.8 (VCC), U4.16 (VCC)
/CAN+: D1.1 (A1), J2.7, TP3.1
/CAN-: D1.2 (A2), J2.2, TP4.1
/MODBUS+: D2.2 (A2), J2.8, TP1.1
/MODBUS-: D2.1 (A1), J2.4, TP2.1
/RS_TNOW: U2.2 (~RE), U2.3 (DE)
GND: A2.3 (GND), A2.8 (GND), A2.13 (GND), A2.18 (GND), A2.23 (GND), A2.28 (GND), A2.33 (AGND), A2.38 (GND), D1.3 (common), D2.3 (common), J2.0 (PAD), J2.3, J2.6, SW1.9, SW1.10, SW1.11, SW1.12, SW1.13, SW1.14, SW1.15, SW1.16, U1.2 (GND), U2.5 (GND), U3.7 (GND), U4.8 (GND), U4.15 (~CE)
unnamed: RN1.2 (R1), SW1.8, U4.6 (D7)
unnamed: RN1.3 (R2), SW1.7, U4.5 (D6)
unnamed: RN1.4 (R3), SW1.6, U4.4 (D5)
unnamed: RN1.5 (R4), SW1.5, U4.3 (D4)
unnamed: RN1.6 (R5), SW1.4, U4.14 (D3)
unnamed: RN1.7 (R6), SW1.3, U4.13 (D2)
unnamed: RN1.8 (R7), SW1.2, U4.12 (D1)
unnamed: RN1.9 (R8), SW1.1, U4.11 (D0)
VCC: J2.1, J2.9

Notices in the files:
hw/breakout/breakout.kicad_pcb:
Licensed under CERN OHL v.1.2
